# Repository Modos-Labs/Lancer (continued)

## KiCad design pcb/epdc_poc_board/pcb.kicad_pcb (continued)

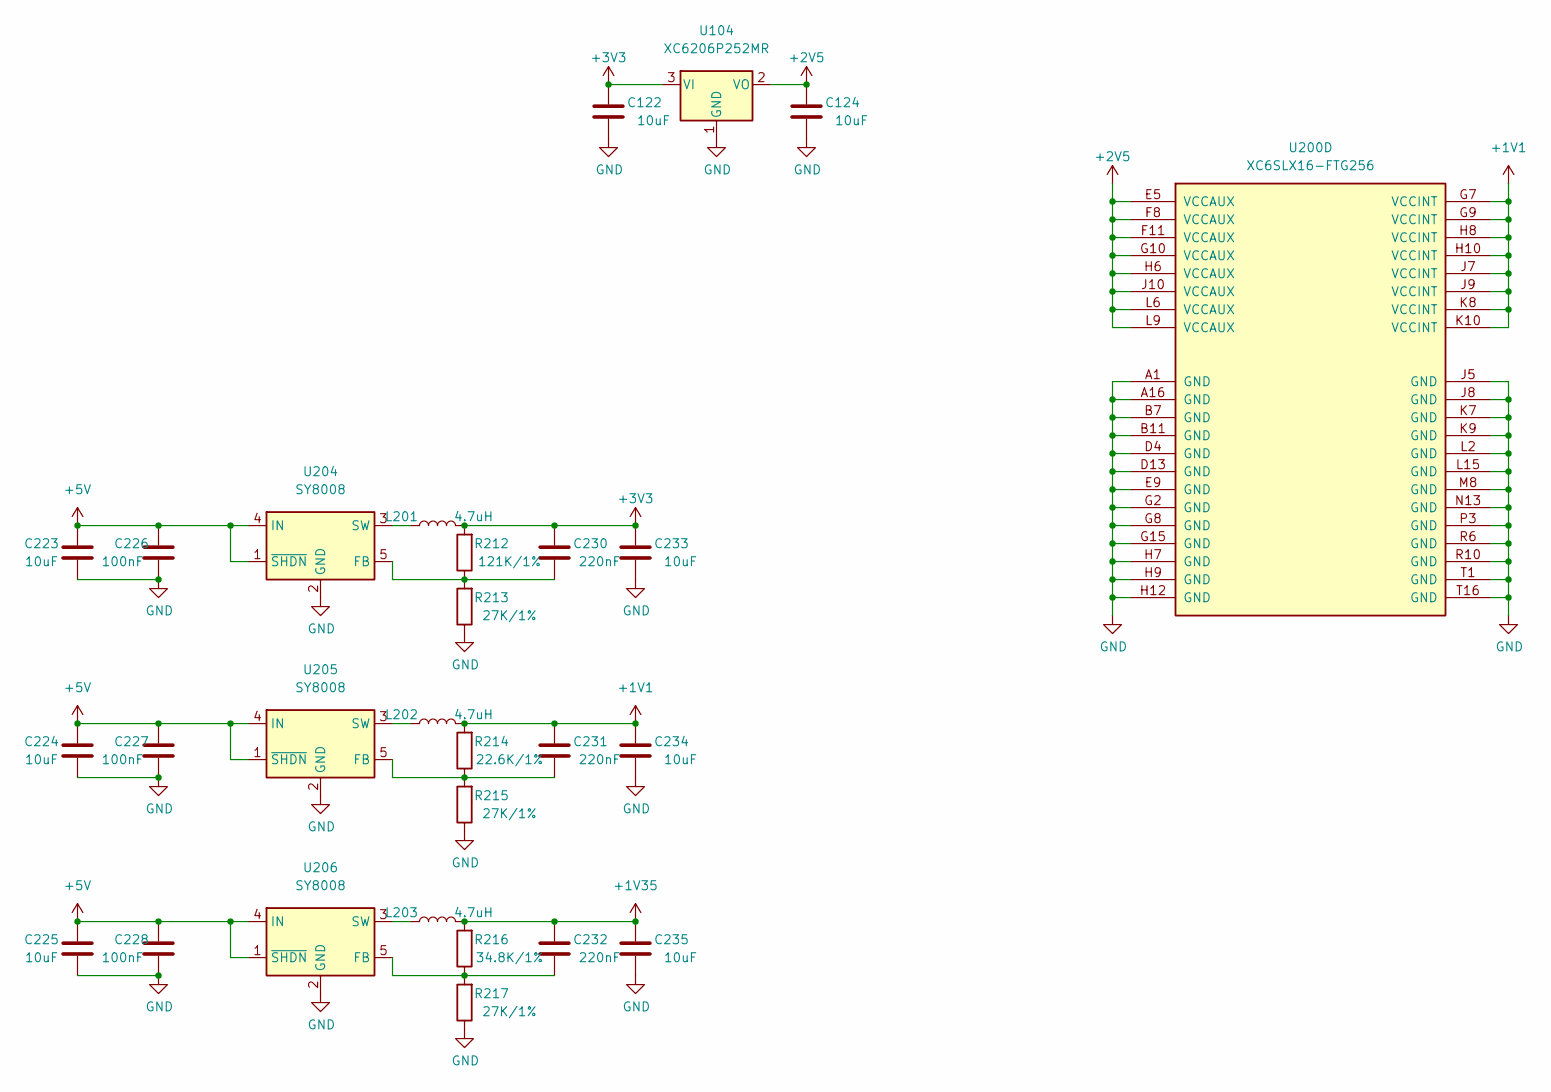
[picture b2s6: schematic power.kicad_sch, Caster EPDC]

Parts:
C122, C124, C223, C224, C225, C233, C234, C235: 10uF; C_0603_1608Metric; LCSC C105490
C226, C227, C228: 100nF; C_0402_1005Metric; LCSC C56392
C230, C231, C232: 220nF; C_0402_1005Metric; LCSC C880414
L201, L202, L203: 4.7uH; L_1212; LCSC C340379
R212: 121K/1%; R_0402_1005Metric; LCSC C112303
R213, R215, R217: 27K/1%; R_0402_1005Metric; LCSC C138022
R214: 22.6K/1%; R_0402_1005Metric; LCSC C477674
R216: 34.8K/1%; R_0402_1005Metric; LCSC C327350
U104: XC6206P252MR; SOT-23; LCSC C15906
U200: XC6SLX16-FTG256; BGA-256_14.0x14.0mm_Layout16x16_P0.8mm_Ball0.45mm_Pad0.32mm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; LCSC C39313
U204, U205, U206: SY8008; TSOT-23-5; LCSC C82161

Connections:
+1V1: C231.2, C234.2, L202.2, R214.2, U200.G7 (VCCINT), U200.G9 (VCCINT), U200.H8 (VCCINT), U200.H10 (VCCINT), U200.J7 (VCCINT), U200.J9 (VCCINT), U200.K8 (VCCINT), U200.K10 (VCCINT); also elsewhere on the board
+1V35: C232.2, C235.2, L203.2, R216.2; also elsewhere on the board
+2V5: C124.2, U104.2 (VO), U200.E5 (VCCAUX), U200.F8 (VCCAUX), U200.F11 (VCCAUX), U200.G10 (VCCAUX), U200.H6 (VCCAUX), U200.J10 (VCCAUX), U200.L6 (VCCAUX), U200.L9 (VCCAUX); also elsewhere on the board
+3V3: C122.2, C230.2, C233.2, L201.2, R212.2, U104.3 (VI); also elsewhere on the board
+5V: C223.2, C224.2, C225.2, C226.2, C227.2, C228.2, U204.1 (~SHDN), U204.4 (IN), U205.1 (~SHDN), U205.4 (IN), U206.1 (~SHDN), U206.4 (IN); also elsewhere on the board
GND: C122.1, C124.1, C223.1, C224.1, C225.1, C226.1, C227.1, C228.1, C233.1, C234.1, C235.1, R213.1, R215.1, R217.1, U104.1 (GND), U200.A1 (GND), U200.A16 (GND), U200.B7 (GND), U200.B11 (GND), U200.D4 (GND), U200.D13 (GND), U200.E9 (GND), U200.G2 (GND), U200.G8 (GND), U200.G15 (GND), U200.H7 (GND), U200.H9 (GND), U200.H12 (GND), U200.J5 (GND), U200.J8 (GND), U200.K7 (GND), U200.K9 (GND), U200.L2 (GND), U200.L15 (GND), U200.M8 (GND), U200.N13 (GND), U200.P3 (GND), U200.R6 (GND), U200.R10 (GND), U200.T1 (GND), U200.T16 (GND), U204.2 (GND), U205.2 (GND), U206.2 (GND); also elsewhere on the board
unnamed: C230.1, R212.1, R213.2, U204.5 (FB)
unnamed: C231.1, R214.1, R215.2, U205.5 (FB)
unnamed: C232.1, R216.1, R217.2, U206.5 (FB)
unnamed: L201.1, U204.3 (SW)
unnamed: L202.1, U205.3 (SW)
unnamed: L203.1, U206.3 (SW)

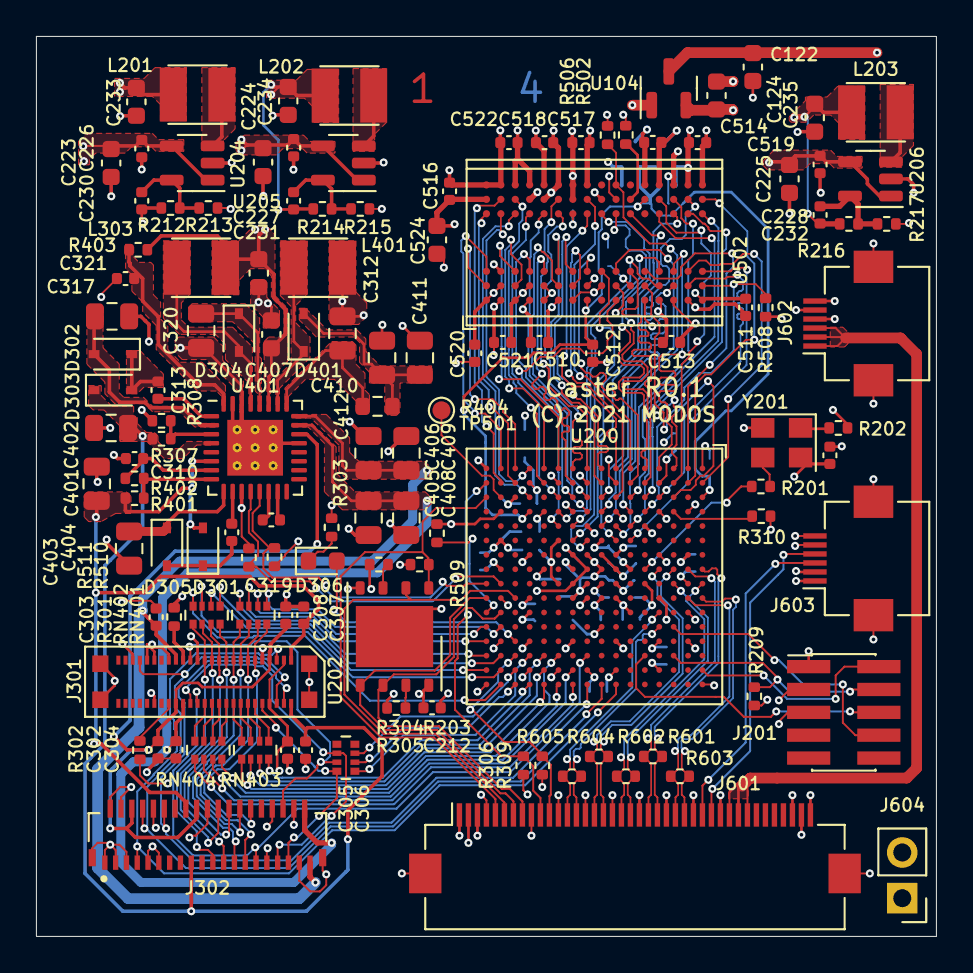
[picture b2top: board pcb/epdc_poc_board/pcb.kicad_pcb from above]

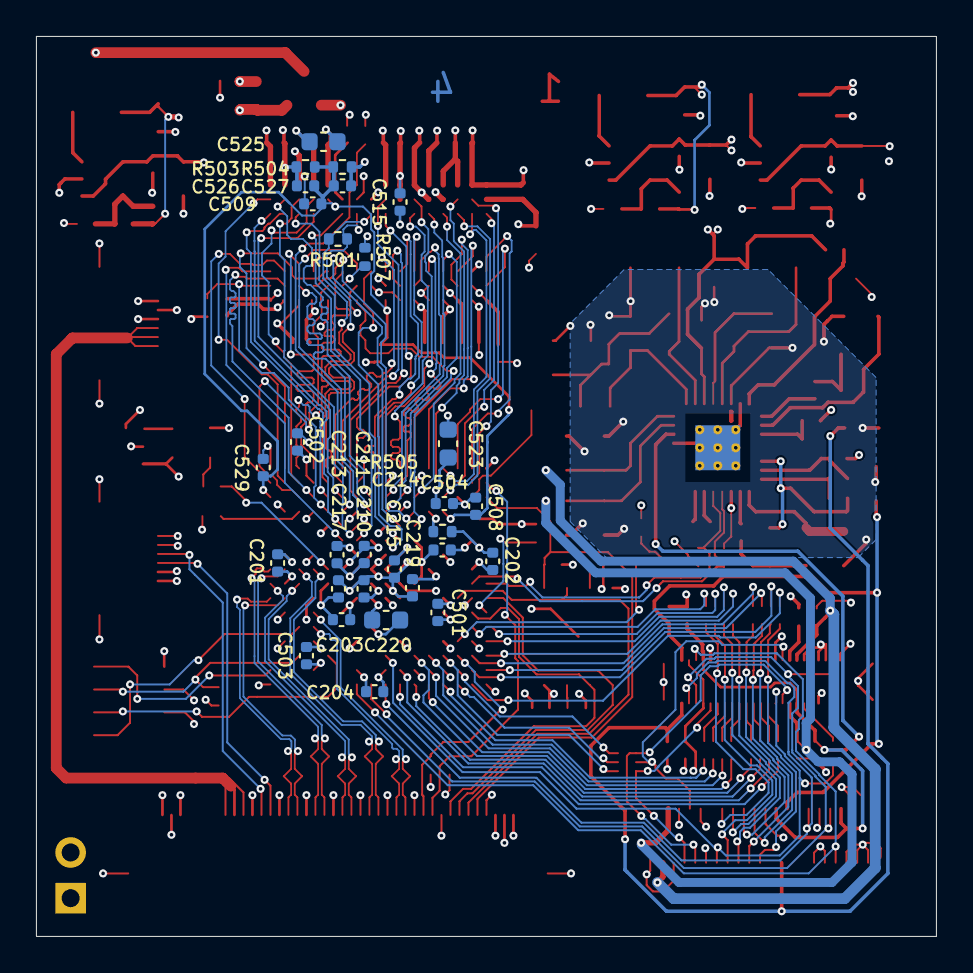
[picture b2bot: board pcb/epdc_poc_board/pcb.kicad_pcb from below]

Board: 4 copper layers, 50.0 x 50.0 mm, 153 parts (29 on the bottom side), 166 nets.

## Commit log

2021-10-10 pcb: move motherboard to a new directory; working on epdc poc board
2021-10-17 - wip epdc poc board, going to remove vga input
2021-10-24 pcb: switch to s6 for epdc board
2021-10-31 pcb: preliminary r0p1 schematics
2021-11-04 pcb: initial placement for mb
2021-11-07 pcb: r0.1 mb routing done
2021-11-14 pcb: mb r0.1, caster r0.1 freeze
2022-01-13 doc: update readme
